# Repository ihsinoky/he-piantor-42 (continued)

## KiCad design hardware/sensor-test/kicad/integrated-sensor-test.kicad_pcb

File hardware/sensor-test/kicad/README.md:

# Sensor-test KiCad project

This directory contains the electrical design for the four-key Hall evaluation board.

## Integrated design

`integrated-sensor-test.kicad_sch` is the review and PCB-source schematic. It combines:

- the RP2040 core, flash, crystal, BOOTSEL, RUN/reset and SWD access from the
  Raspberry Pi minimal-design baseline;
- the USB-C sink, USB ESD, 3.3 V regulator and always-on power indicator;
- switched `HALL_5V`, four DRV5055 sensors, TMUX1208, and the protected
  `ADC_SENSE` input; and
- a GPIO11 evaluation-status LED. The production layer RGB LED (`GPIO8`–`GPIO10`)
  remains reserved and is deliberately not fitted on this evaluation board.

The Hall control nets are connected directly at the RP2040 pins rather than via
an external-controller placeholder: GPIO2=`MUX_A0`, GPIO3=`MUX_A1`,
GPIO4=`MUX_A2`, GPIO5=`MUX_EN0`, GPIO7=`HALL_PWR_EN`, and GPIO26/ADC0=`ADC_SENSE`.

The three older schematics remain as traceable source blocks and standalone ERC
fixtures. Do not use them independently as the PCB source.

## Footprint dependency bootstrap

`footprint-dependencies.json` is mechanically generated from the integrated
schematic by `inventory_footprints.py`. The manually dispatched
`bootstrap-kicad-footprints` workflow exports only the listed official
footprints from `kicad/kicad:9.0.9`. It discovers and validates each source path
inside the image rather than assuming the image layout, preserves the exported
bytes, and publishes provenance plus SHA-256 hashes in the
`issue-11-kicad-9.0.9-footprints` artifact. The workflow runs automatically on
the Issue #11 pull request (and can also be dispatched manually) and includes
the license/attribution file supplied by the image package.

The artifact must be reviewed and copied to
`hardware/lib/third_party/kicad-9-footprints/` before the standard logical
libraries can be rebound in `fp-lib-table`. Do not substitute generated or
look-alike geometry when the official artifact is unavailable.

## Scope

This milestone stops at an ERC-clean integrated schematic. PCB placement,
routing, Gerbers and assembly outputs are intentionally deferred. Do not order
boards from this directory yet.

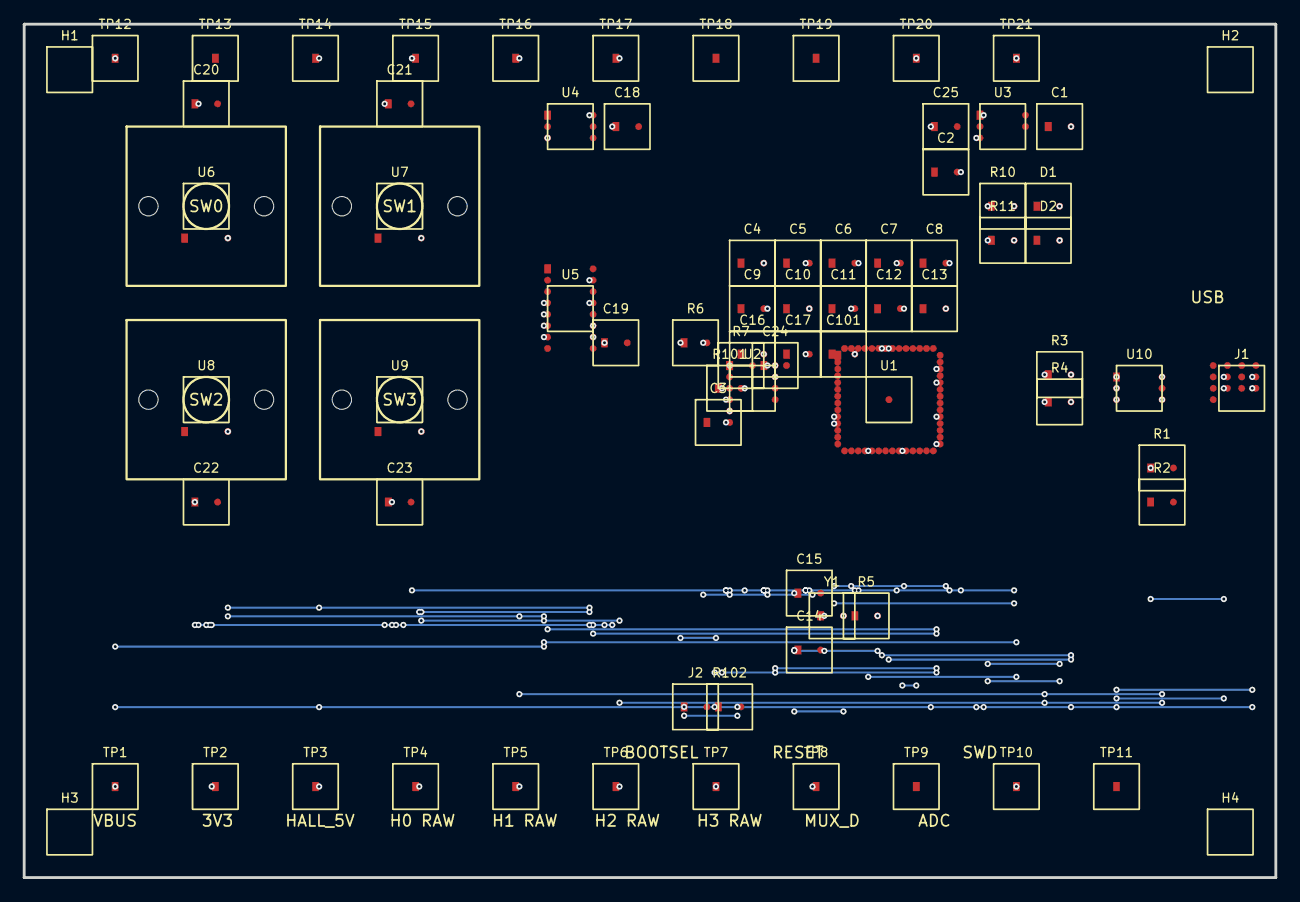
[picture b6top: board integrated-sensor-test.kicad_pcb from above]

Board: 4 copper layers, 110.0 x 75.0 mm, 77 parts (0 on the bottom side), 32 nets.

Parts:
C1, C2, C18, C25: 1u; C_0603_1608Metric
C3, C4, C5, C6, C7, C8, C10, C12, C13, C16: 100n; C_0402_1005Metric
C9, C11: 1u; C_0402_1005Metric
C14, C15: 15p; C_0402_1005Metric
C17, C101: 10u; C_0805_2012Metric
C19, C20, C21, C22, C23: 100n; C_0603_1608Metric
C24: 1n; C_0603_1608Metric
D1: POWER_GREEN; LED_0603_1608Metric
D2: STATUS_GREEN; LED_0603_1608Metric
H1, H2, H3, H4: MountingHole; MountingHole_2.7mm_M2.5
J1: TYPE-C-31-M-12; USB_C_Receptacle_HRO_TYPE-C-31-M-12
J2: Conn_01x02; PinHeader_1x02_P2.54mm_Vertical
R1, R2: 5.1k; R_0603_1608Metric
R3, R4: 27; C_0402_1005Metric
R5: 1k; R_0402_1005Metric
R6: 6.8k; R_0603_1608Metric
R7: 10k; R_0603_1608Metric
R10, R11: 1.5k; R_0603_1608Metric
R101: DNF; C_0402_1005Metric
R102: 1k; C_0402_1005Metric
TP1, TP14: VBUS; TestPoint_Pad_D1.5mm
TP2: HALL_5V; TestPoint_Pad_D1.5mm
TP3: H0_RAW; TestPoint_Pad_D1.5mm
TP4: H1_RAW; TestPoint_Pad_D1.5mm
TP5: H2_RAW; TestPoint_Pad_D1.5mm
TP6: H3_RAW; TestPoint_Pad_D1.5mm
TP7: MUX_D; TestPoint_Pad_D1.5mm
TP8: ADC_SENSE; TestPoint_Pad_D1.5mm
TP9, TP18: GND; TestPoint_Pad_D1.5mm
TP10: MUX_S5_SPARE; TestPoint_Pad_D1.5mm
TP11: MUX_S6_SPARE; TestPoint_Pad_D1.5mm
TP12: MUX_S7_SPARE; TestPoint_Pad_D1.5mm
TP13: MUX_S8_SPARE; TestPoint_Pad_D1.5mm
TP15: +3V3; TestPoint_Pad_D1.5mm
TP16: USB_D+_PROTECTED; TestPoint_Pad_D1.5mm
TP17: USB_D-_PROTECTED; TestPoint_Pad_D1.5mm
TP19: SWDIO; TestPoint_Pad_D1.5mm
TP20: SWCLK; TestPoint_Pad_D1.5mm
TP21: RUN; TestPoint_Pad_D1.5mm
U1: RP2040; RP2040-QFN-56
U2: W25Q16JVUXIQ; USON-8_UX_2x3x0p6_WIN
U3: AP2112K-3.3TRG1; SOT-23-5
U4: TPS22919DCKR; SOT-363_SC-70-6
U5: TMUX1208PWR; TSSOP-16_4.4x5mm_P0.65mm
U6, U7, U8, U9: DRV5055A3QDBZR; SW_MX_HE_0deg_1u
U10: USBLC6-2SC6; SOT-23-6
Y1: ABM8-272-T3; Crystal_SMD_Abracon_ABM8G-2Pin_3.2x2.5mm

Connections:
+1V1: C11.2, C12.2, C13.2, U1.19
+3V3: C2.2, C3.2, C4.2, C5.2, C6.2, C7.2, C8.2, C9.2, C10.2, C16.2, C17.2, C101.2, R10.2, R101.2, TP15.1, U2.4, U2.9
ADC_SENSE: C24.1, R6.2, R7.1, TP8.1
CC1: J1.A7, R1.1
GND: C1.1, C2.1, C3.1, C4.1, C5.1, C6.1, C7.1, C8.1, C9.1, C10.1, C11.1, C12.1, C13.1, C14.2, C15.2, C16.1, C17.1, C18.2, C19.2, C20.2, C21.2, C22.2, C23.2, C24.2, C25.2, C101.1, D1.1, D2.1, R1.2, R2.2, R7.2, TP9.1, TP18.1, U1.45, U2.8, U5.13, U6.1, U7.1, U8.1, U9.1, U10.5
GPIO11: R11.2, U1.18
H0_RAW: TP3.1, U5.10, U6.2
H1_RAW: TP4.1, U5.12, U7.2
H2_RAW: TP5.1, U5.7, U8.2
H3_RAW: TP6.1, U5.6, U9.2
HALL_5V: C18.1, C19.1, C20.1, C21.1, C22.1, C23.1, TP2.1, U4.4, U5.14, U6.3, U7.3, U8.3, U9.3
HALL_PWR_EN: U1.30, U4.3
MUX_A2: U1.34, U5.15
MUX_D: R6.1, TP7.1
MUX_S5_SPARE: TP10.1, U5.5
MUX_S7_SPARE: TP12.1, U5.4
unnamed: C14.1, R5.2, Y1.1
unnamed: R4.2, U1.40
unnamed: R3.2, U1.41
PWR_LED_A: D1.2, R10.1
QSPI_SD3: U1.26, U2.5
QSPI_SS: R101.1, R102.1, U1.24, U2.6
RUN: TP21.1, U1.51
STATUS_LED_A: D2.2, R11.1
SWCLK: TP20.1, U1.56
USB_D+_CONN: J1.A6, U10.1
USB_D+_PROTECTED: R3.1, TP16.1, U10.6
USB_D-_CONN: J1.A5, U10.3
USB_D-_PROTECTED: R4.1, TP17.1, U10.4
VBUS: C1.2, C25.1, J1.A8, TP1.1, TP14.1, U3.1, U3.3, U10.2
XIN: C15.1, Y1.2
~USB_BOOT: J2.1, R102.2

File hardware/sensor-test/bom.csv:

block,reference,qty,manufacturer,mpn,lcsc,package,value_or_note,population
MCU,U1,1,Raspberry Pi,RP2040,C2040,LQFN-56,MCU,baseline
Flash,U2,1,Winbond,W25Q16JVUXIQ,C2843335,USON-8-EP(2x3),16Mbit QSPI,baseline
Crystal,Y1,1,Abracon,ABM8-272-T3,C20625731,SMD3225-4P,12MHz 10pF,baseline
Logic regulator,U3,1,Diodes Inc.,AP2112K-3.3TRG1,C51118,SOT-25-5,3.3V 600mA,baseline
Logic regulator input capacitor,C1,1,TBD,TBD,TBD,0603,1uF X7R VBUS-to-GND,baseline
Logic regulator output capacitor,C2,1,TBD,TBD,TBD,0603,1uF X7R 3V3-to-GND,baseline
Hall load switch,U4,1,Texas Instruments,TPS22919DCKR,C2149796,SC-70-6,switched HALL_5V,baseline
Hall switch input decoupling,C25,1,TBD,TBD,TBD,0603,1uF X7R VBUS-to-GND,baseline
Hall rail bulk/decoupling,C18,1,TBD,TBD,TBD,0603,1uF X7R HALL_5V-to-GND,baseline
Analog mux,U5,1,Texas Instruments,TMUX1208PWR,C494728,TSSOP-16,8:1 mux,baseline
Hall sensor,U6-U9,4,Texas Instruments,DRV5055A3QDBZR,C266128,SOT-23,+/-85mT 25mV/mT@5V,reference build
USB connector,J1,1,Korean Hroparts Elec,TYPE-C-31-M-12,C165948,SMD,USB-C 16P,baseline
USB ESD,U10,1,STMicroelectronics,USBLC6-2SC6,C7519,SOT-23-6L,USB 2.0 two-line ESD protection,baseline
USB CC resistors,R1 R2,2,TBD,TBD,TBD,0603,5.1k 1%,baseline
USB series resistors,R3 R4,2,TBD,TBD,TBD,0603,27R 1%,baseline
Crystal series resistor,R5,1,TBD,TBD,TBD,0603,1k 1%,baseline
Flash decoupling,C3,1,TBD,TBD,TBD,0402,100nF X7R,baseline
RP2040 high-frequency decoupling,C4-C8 C10 C12 C13 C16,9,TBD,TBD,TBD,0402,100nF X7R,baseline
RP2040 regulator decoupling,C9 C11,2,TBD,TBD,TBD,0402,1uF X7R,baseline
RP2040 bulk capacitor,C17,1,TBD,TBD,TBD,0805,10uF X7R,baseline
QSPI optional resistor,R8,1,TBD,TBD,TBD,0603,DNF,do not fit
BOOTSEL series resistor,R9,1,TBD,TBD,TBD,0603,1k 1%,baseline
Crystal load capacitors,C14 C15,2,TBD,TBD,TBD,0402,15pF C0G,baseline
ADC divider top,R6,1,TBD,TBD,TBD,0603,6.8k 1%,baseline
ADC divider bottom,R7,1,TBD,TBD,TBD,0603,10k 1%,baseline
ADC filter,C24,1,TBD,TBD,TBD,0603,1nF C0G/X7R,baseline
Hall decoupling,C20-C23,4,TBD,TBD,TBD,0603,100nF X7R,baseline
Mux decoupling,C19,1,TBD,TBD,TBD,0603,100nF X7R,baseline
Power LED,D1,1,TBD,TBD,TBD,0603,green,baseline
Power LED resistor,R10,1,TBD,TBD,TBD,0603,1.5k target <1mA,baseline
Status LED,D2,1,TBD,TBD,TBD,0603,GPIO11 diagnostic LED,baseline
Status LED resistor,R11,1,TBD,TBD,TBD,0603,1.5k target <1mA,baseline
BOOTSEL switch,SW1,1,TBD,TBD,TBD,PTS810-compatible SMD tact,QSPI_SS to GND through R9,baseline
RESET switch,SW2,1,TBD,TBD,TBD,PTS810-compatible SMD tact,RUN to GND,baseline

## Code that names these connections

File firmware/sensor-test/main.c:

#include <stdbool.h>
#include <stdint.h>
#include <stdio.h>

#include "hardware/adc.h"
#include "pico/stdio_usb.h"
#include "pico/stdlib.h"

enum {
    PIN_MUX_A0 = 2,
    PIN_MUX_A1 = 3,
    PIN_MUX_A2 = 4,
    PIN_MUX_EN0 = 5,
    PIN_HALL_PWR_EN = 7,
    PIN_STATUS_LED = 11,
    PIN_ADC0 = 26,
};

enum {
    ADC_INPUT_0 = 0,
    MUX_ADDRESS_COUNT = 4,
    MUX_SETTLE_US = 20,
    ADC_SAMPLES_PER_KEY = 8,
    USB_WAIT_MS = 3000,
    HALL_POWER_SETTLE_MS = 10,
    FRAME_PERIOD_MS = 10,
};

static void init_output(uint pin, bool value) {
    gpio_init(pin);
    gpio_set_dir(pin, GPIO_OUT);
    gpio_put(pin, value);
}

static void mux_set_address(uint8_t address) {
    gpio_put(PIN_MUX_A0, (address >> 0) & 1u);
    gpio_put(PIN_MUX_A1, (address >> 1) & 1u);
    gpio_put(PIN_MUX_A2, (address >> 2) & 1u);
}

static uint16_t read_adc_average(void) {
    // First conversion after an analog-mux transition is intentionally discarded.
    (void)adc_read();

    uint32_t sum = 0;
    for (uint i = 0; i < ADC_SAMPLES_PER_KEY; ++i) {
        sum += adc_read();
    }
    return (uint16_t)((sum + ADC_SAMPLES_PER_KEY / 2u) / ADC_SAMPLES_PER_KEY);
}

int main(void) {
    // Keep the Hall rail and mux disabled from the first software-controlled state.
    init_output(PIN_HALL_PWR_EN, false);
    init_output(PIN_MUX_EN0, false);
    init_output(PIN_MUX_A0, false);
    init_output(PIN_MUX_A1, false);
    init_output(PIN_MUX_A2, false);
    init_output(PIN_STATUS_LED, false);

    adc_init();
    adc_gpio_init(PIN_ADC0);
    adc_select_input(ADC_INPUT_0);

    stdio_init_all();

    // Give USB CDC time to enumerate, but do not require a host for board operation.
    absolute_time_t usb_deadline = make_timeout_time_ms(USB_WAIT_MS);
    while (!stdio_usb_connected() && !time_reached(usb_deadline)) {
        sleep_ms(10);
    }

    gpio_put(PIN_HALL_PWR_EN, true);
    sleep_ms(HALL_POWER_SETTLE_MS);
    gpio_put(PIN_MUX_EN0, true);
    gpio_put(PIN_STATUS_LED, true);

    printf("# he-piantor-42 sensor-test\n");
    printf("# settle_us=%u,samples_per_key=%u\n", MUX_SETTLE_US, ADC_SAMPLES_PER_KEY);
    printf("timestamp_us,key,mux_address,adc_raw,hall_power,test_marker\n");

    while (true) {
        absolute_time_t frame_start = get_absolute_time();

        for (uint8_t address = 0; address < MUX_ADDRESS_COUNT; ++address) {
            mux_set_address(address);
            busy_wait_us_32(MUX_SETTLE_US);

            const uint16_t raw = read_adc_average();
            const uint64_t timestamp_us = time_us_64();

            printf("%llu,%u,%u,%u,1,stream\n",
                   (unsigned long long)timestamp_us,
                   (unsigned)address,
                   (unsigned)address,
                   (unsigned)raw);
        }

        // Keep the initial logger bandwidth modest and deterministic.
        const int64_t elapsed_us = absolute_time_diff_us(frame_start, get_absolute_time());
        const int64_t target_us = (int64_t)FRAME_PERIOD_MS * 1000;
        if (elapsed_us < target_us) {
            sleep_us((uint32_t)(target_us - elapsed_us));
        }
    }
}
